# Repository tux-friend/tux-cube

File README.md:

# Physics Sensor Cube ESP32-Tux³

11.04.23 Idea for own ESP32 PCB Design  
15.04.23 First sketches with KiCad  
16.04.23 Idea for physics sensor cube Tux³ and first sketches  
17.04.23 Design and order of v0.1 PCB  
22.04.23 First prototype and proof of concept  
23.04.23 Case v0.1  
25.04.23 Design and order of v0.2 PCB  
25.04.23 Case v0.2  
29.04.23 Software v0.1  
03.05.23 Arrival of PCB v0.1 + v0.2  
10.05.23 Arrival of all parts for PCB, first working ESP32-C3 board  
11.05.23 Order of 30 pcs v0.2 PCB on JLCPCB  
12.05.23 Forth ESP32-C3 board completed  
13.05.23 Case v0.3  
14.05.23 First full prototype &rarr; case too small  
17.05.23 Case v0.4  
21.05.23 ESP32-C3-Tux Mini PCB 20x20mm  
22.05.23 Case v0.5  
27.05.23 Finished DIY Reflow Heat Plate  
31.05.23 Put ESP32-Tux on Tindie and got promotion by [hackster.io](https://www.hackster.io/news/the-lifex-esp32-tux-mini-offers-a-tiny-path-to-energy-harvesting-experimentation-with-an-esp32-c3-0470bf924f33) :-)  
03.06.23 Finished 12 ESP32-Tux Dev boards for Tindie orders  
13.02.24 Designed a ESP32-Tux Board with TP4056 Charging circuit  
15.03.26 Finally got time to get back in the project and designed a new Dev Board with ESP32-C5 chip  

This is an idea I had for some time after playing around with the ESP32 together with sensors, micropython and Phyphox. I started designing a PCB by my own for an ESP32-C3 chip. I want it to be as small as possible and also solar powered. The cube should be energy ,self-sufficient' and used for teaching physics. 

The cube should have the following sensors:
- Temperature, pressure and humidity sensor &rarr; BME280
- Gyroscope for acceleration and orientation measurements &rarr; MPU9250
- Optical/Light sensor (measuring Lux) &rarr; VEML7700
- 2 connectors for temperature probes (DS18B20)
- Voltage and current meter &rarr; INA219
- Time of flight sensor for measuring distances &rarr; VL53L1X
- optional: magnetometer & microphone for sound measurements

In addition the cube should have:
- OLED Display for showing current measurement data/sensor
- RGB-LED (e.g. for showing battery status)
- Push button for changing the sensor/measurement
- Solar cell and LiPo battery
- Pin-header for connecting to cube to a breadboard and use the GPIO Pins
- Mounting nut for placing the cube on a tripod
- On/Off-Button
- optional: buzzer for sound output

I aim for a 35x35x35mm cube with 3D printed case. The case should be robust - so that it can fall from a building and be undamaged... Hope to be able to do this project. 

My inspiration come from the [ESP32-Picoclick-C3](https://github.com/makermoekoe/Picoclick-C3), [BQ25504 Solar Cell LiPo Charger](https://hackaday.io/project/158837-ultra-low-power-lipo-charger-via-energy-harvesting), [01Space-ESP32-C3](https://github.com/01Space/ESP32-C3-0.42LCD) and the [Wemos C3 Pico](https://www.wemos.cc/en/latest/c3/c3_pico.html).

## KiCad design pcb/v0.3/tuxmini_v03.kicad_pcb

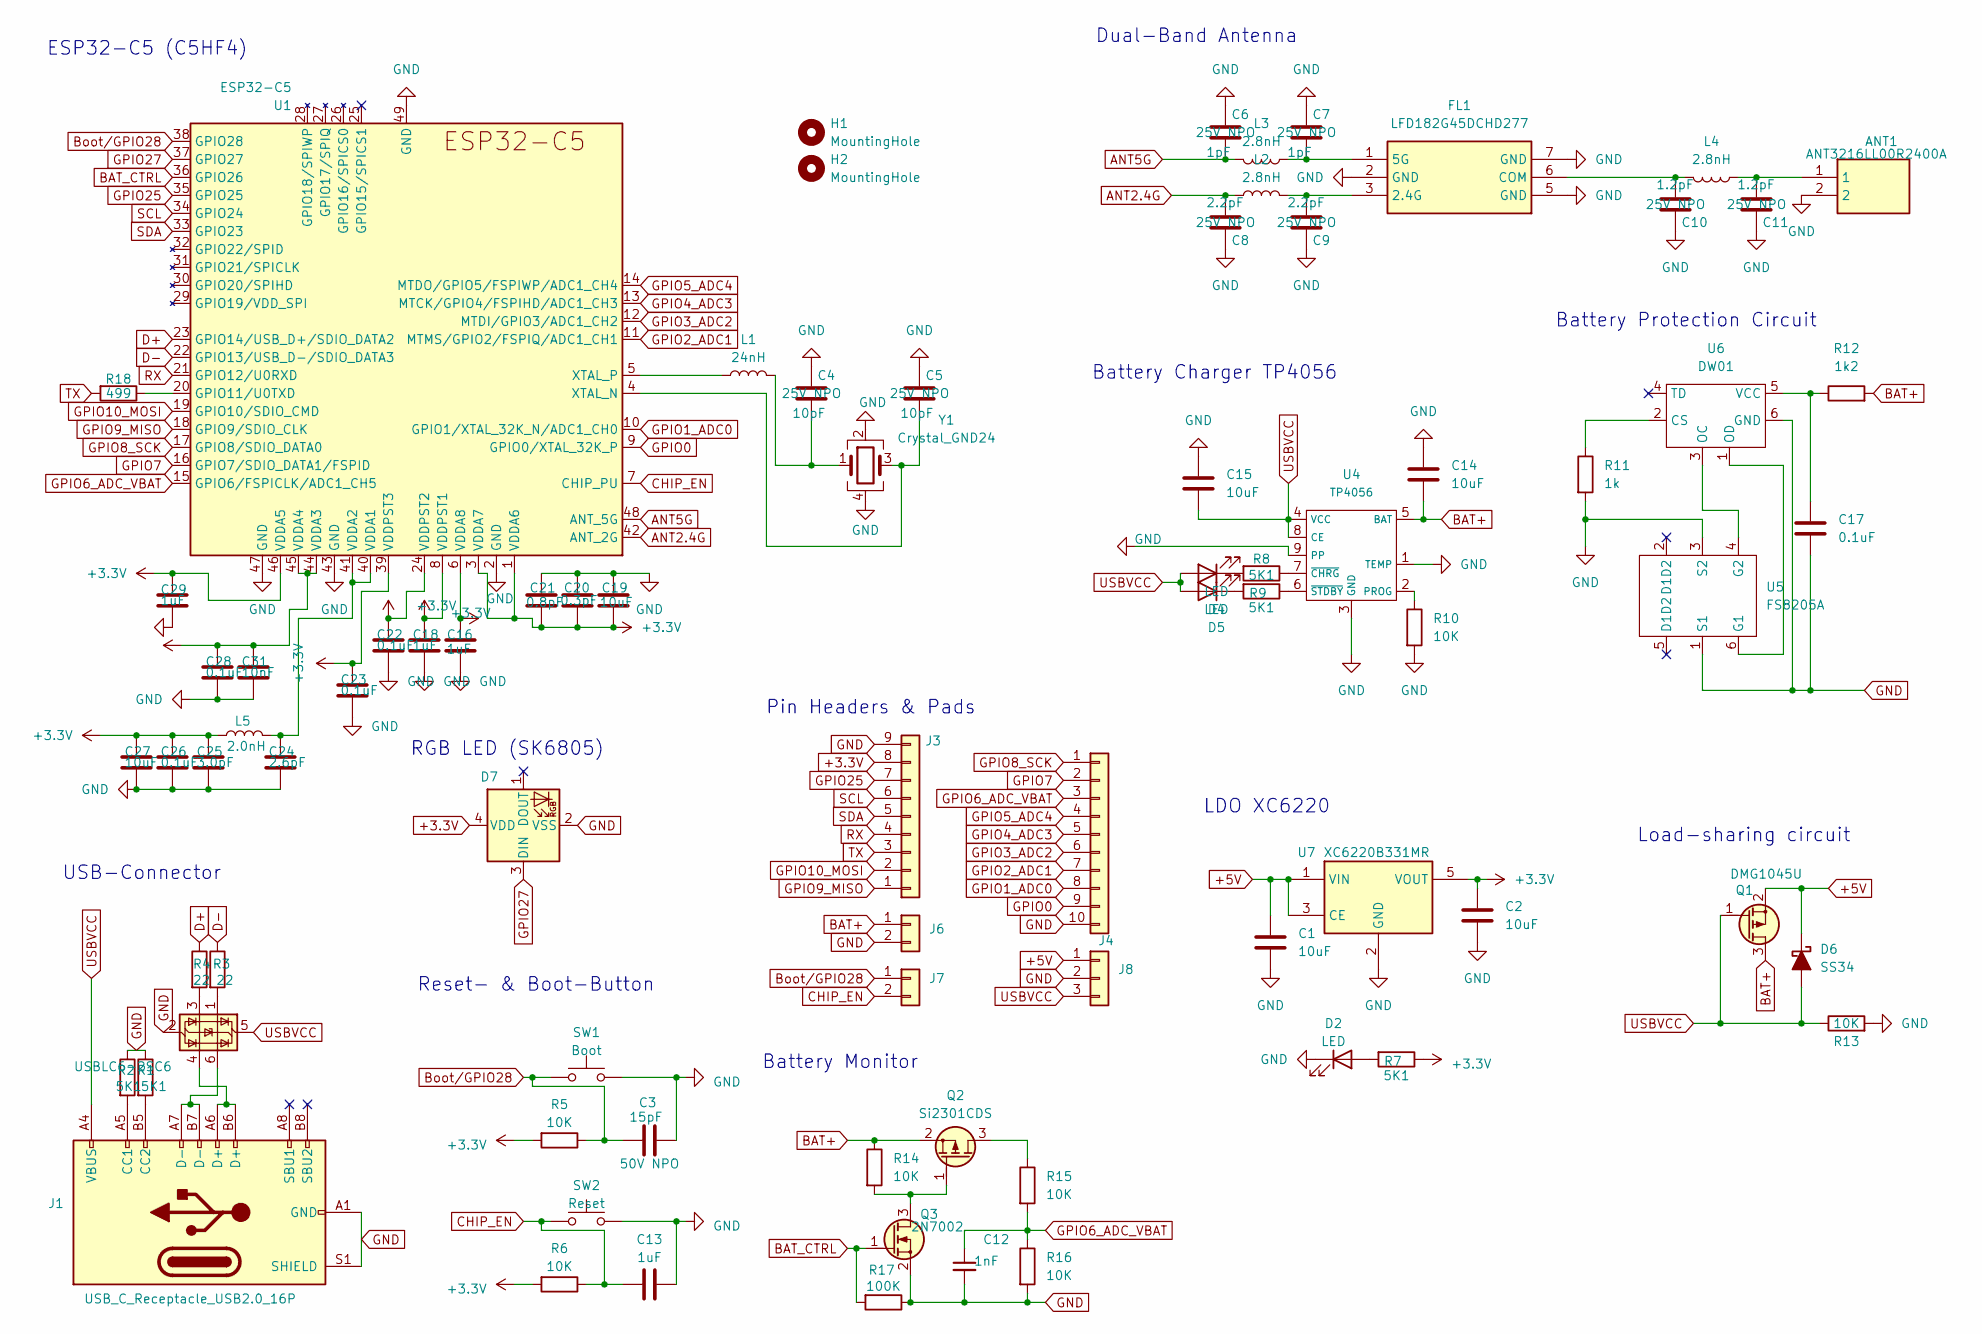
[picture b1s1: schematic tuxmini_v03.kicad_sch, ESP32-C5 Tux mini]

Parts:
ANT1: ANT3216LL00R2400A; Johanson_2450AT18x100; Mouser Part Number 603-ANT3216LL00R2400
C1, C2, C14, C15, C19, C27: 10uF; C_0402_1005Metric
C3: 15pF; C_0402_1005Metric
C4, C5: 10pF; C_0402_1005Metric
C6, C7: 1pF; C_0402_1005Metric
C8, C9: 2.2pF; C_0402_1005Metric
C10, C11: 1.2pF; C_0402_1005Metric
C12: 1nF; C_0402_1005Metric; Tolerance 100%
C13, C16, C18, C29: 1uF; C_0402_1005Metric
C17, C22, C23, C26, C28: 0.1uF; C_0402_1005Metric
C20: 0.3pF; C_0402_1005Metric
C21: 0.8pF; C_0402_1005Metric
C24: 2.6pF; C_0402_1005Metric
C25: 3.0pF; C_0402_1005Metric
C31: 10nF; C_0402_1005Metric
D2, D4, D5: LED; LED_0402_1005Metric
D6: SS34; D_SOD-523
D7: SK6805; LED_SK6812_EC15_1.5x1.5mm
FL1: LFD182G45DCHD277; Manufacturer_Part_Number LFD182G45DCHD277
H1, H2: MountingHole; MountingHole_2.5mm_Pad_Via
J1: USB_C_Receptacle_USB2.0_16P; USB_C_Receptacle_Palconn_UTC16-G
J3: Conn_01x09; PinHeader_1x09_P2.54mm_Vertical
J4: Conn_01x10; PinHeader_1x10_P2.54mm_Vertical
J6: Conn_01x02; PinHeader_1x02_P2.54mm_Vertical; Part Number 1-0201FBV0T
J7: Conn_01x02; PinHeader_1x02_P2.54mm_Vertical
J8: Conn_01x03; PinHeader_1x03_P2.54mm_Vertical
L1: 24nH; L_0402_1005Metric
L2, L3, L4: 2.8nH; L_0402_1005Metric
L5: 2.0nH; L_0402_1005Metric
Q1: DMG1045U; SOT-23
Q2: Si2301CDS; SOT-23
Q3: 2N7002; SOT-23
R1, R2, R7, R8, R9: 5K1; R_0402_1005Metric
R3, R4: 22; R_0402_1005Metric
R5, R6, R10, R13, R14, R15, R16: 10K; R_0402_1005Metric
R11: 1k; R_0402_1005Metric
R12: 1k2; R_0402_1005Metric
R17: 100K; R_0402_1005Metric
R18: 499; R_0402_1005Metric
SW1: Boot; SW_Push_1P1T_NO_CK_KMR2
SW2: Reset; SW_Push_1P1T_NO_CK_KMR2
U1: ESP32-C5; QFN-48-1EP_6x6mm_P0.4mm_EP4.6x4.6mm
U2: USBLC6-2SC6; SOT-23-6
U4: TP4056; SOIC-8-1EP_3.9x4.9mm_P1.27mm_EP2.29x3mm
U5: FS8205A; SOT-23-6
U6: DW01; SOT-23-6
U7: XC6220B331MR; SOT-23-5
Y1: Crystal_GND24; Crystal_SMD_2016-4Pin_2.0x1.6mm

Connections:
+3.3V: C2.1, C16.1, C18.1, C19.2, C20.2, C21.2, C22.1, C23.1, C25.1, C26.1, C27.1, C28.1, C29.1, C31.1, D7.4 (VDD), J3.8, L5.2, R5.2, R6.2, R7.1, U1.1 (VDDA6), U1.3 (VDDA7), U1.6 (VDDA8), U1.8 (VDDPST1), U1.24 (VDDPST2), U1.39 (VDDPST3), U1.44 (VDDA3), U1.45 (VDDA4), U1.46 (VDDA5), U7.5 (VOUT)
+5V: C1.1, D6.1 (K), J8.1, Q1.2 (S), U7.1 (VIN), U7.3 (CE)
ANT2.4G: C8.2, L2.2, U1.42 (ANT_2G)
ANT5G: C6.2, L3.2, U1.48 (ANT_5G)
BAT+: C14.2, J6.1, Q1.3 (D), Q2.2 (S), R12.2, R14.1, U4.5 (BAT)
BAT_CTRL: Q3.1 (G), R17.2, U1.36 (GPIO26)
Boot/GPIO28: C3.1, J7.1, R5.1, SW1.1, U1.38 (GPIO28)
CHIP_EN: C13.1, J7.2, R6.1, SW2.1, U1.7 (CHIP_PU)
D+: R4.1, U1.23 (GPIO14/USB_D+/SDIO_DATA2)
D-: R3.1, U1.22 (GPIO13/USB_D-/SDIO_DATA3)
GND: ANT1.2, C1.2, C2.2, C3.2, C4.1, C5.1, C6.1, C7.1, C8.1, C9.1, C10.1, C11.1, C12.2, C13.2, C14.1, C15.1, C16.2, C17.2, C18.2, C19.1, C20.1, C21.1, C22.2, C23.2, C24.2, C25.2, C26.2, C27.2, C28.2, C29.2, C31.2, D2.1 (K), D7.2 (VSS), FL1.2 (GND), FL1.5 (GND), FL1.7 (GND), J1.A1 (GND), J1.A12 (GND), J1.B1 (GND), J1.B12 (GND), J1.S1 (SHIELD), J3.9, J4.10, J6.2, J8.2, Q3.2 (S), R1.1, R2.1, R10.2, R11.2, R13.2, R16.2, R17.1, SW1.2, SW2.2, U1.2 (GND), U1.43 (GND), U1.47 (GND), U1.49 (GND), U2.2 (GND), U4.1 (TEMP), U4.3 (GND), U4.9 (PP), U5.1 (S1), U5.3 (S2), U6.6 (GND), U7.2 (GND), Y1.2, Y1.4
GPIO0: J4.9, U1.9 (GPIO0/XTAL_32K_P)
GPIO1_ADC0: J4.8, U1.10 (GPIO1/XTAL_32K_N/ADC1_CH0)
GPIO2_ADC1: J4.7, U1.11 (MTMS/GPIO2/FSPIQ/ADC1_CH1)
GPIO3_ADC2: J4.6, U1.12 (MTDI/GPIO3/ADC1_CH2)
GPIO4_ADC3: J4.5, U1.13 (MTCK/GPIO4/FSPIHD/ADC1_CH3)
GPIO5_ADC4: J4.4, U1.14 (MTDO/GPIO5/FSPIWP/ADC1_CH4)
GPIO6_ADC_VBAT: C12.1, J4.3, R15.2, R16.1, U1.15 (GPIO6/FSPICLK/ADC1_CH5)
GPIO7: J4.2, U1.16 (GPIO7/SDIO_DATA1/FSPID)
GPIO8_SCK: J4.1, U1.17 (GPIO8/SDIO_DATA0)
GPIO9_MISO: J3.1, U1.18 (GPIO9/SDIO_CLK)
GPIO10_MOSI: J3.2, U1.19 (GPIO10/SDIO_CMD)
GPIO25: J3.7, U1.35 (GPIO25)
GPIO27: D7.3 (DIN), U1.37 (GPIO27)
unnamed: ANT1.1, C11.2, L4.2
unnamed: C4.2, L1.2, Y1.1
unnamed: D2.2 (A), R7.2
unnamed: D4.1 (K), R8.2
unnamed: D5.1 (K), R9.2
unnamed: C9.2, FL1.3 (2.4G), L2.1
unnamed: C7.2, FL1.1 (5G), L3.1
unnamed: C10.2, FL1.6 (COM), L4.1
unnamed: J1.A5 (CC1), R2.2
unnamed: J1.B5 (CC2), R1.2
unnamed: J1.A6 (D+), J1.B6 (D+), U2.4 (I/O2)
unnamed: J1.A7 (D-), J1.B7 (D-), U2.6 (I/O1)
unnamed: Q2.3 (D), R15.1
unnamed: Q2.1 (G), Q3.3 (D), R14.2
unnamed: R3.2, U2.1 (I/O1)
unnamed: R4.2, U2.3 (I/O2)
unnamed: R18.1, U1.20 (GPIO11/U0TXD)
unnamed: C24.1, L5.1, U1.40 (VDDA1), U1.41 (VDDA2)
unnamed: C5.2, U1.4 (XTAL_N), Y1.3
unnamed: L1.1, U1.5 (XTAL_P)
unnamed: R10.1, U4.2 (PROG)
unnamed: R8.1, U4.7 (~CHRG)
unnamed: R9.1, U4.6 (~STDBY)
unnamed: U5.6 (G1), U6.1 (OD)
unnamed: U5.4 (G2), U6.3 (OC)
unnamed: R11.1, U6.2 (CS)
unnamed: C17.1, R12.1, U6.5 (VCC)
RX: J3.4, U1.21 (GPIO12/U0RXD)
SCL: J3.6, U1.34 (GPIO24)
SDA: J3.5, U1.33 (GPIO23)
TX: J3.3, R18.2
USBVCC: C15.2, D4.2 (A), D5.2 (A), D6.2 (A), J1.A4 (VBUS), J1.A9 (VBUS), J1.B4 (VBUS), J1.B9 (VBUS), J8.3, Q1.1 (G), R13.1, U2.5 (VBUS), U4.4 (VCC), U4.8 (CE)

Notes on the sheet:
Reset- & Boot-Button
Battery Monitor
Battery Protection Circuit
LDO XC6220
Load-sharing circuit
Pin Headers & Pads
RGB LED (SK6805)
USB-Connector
ESP32-C5 (C5HF4)
Battery Charger TP4056
Dual-Band Antenna

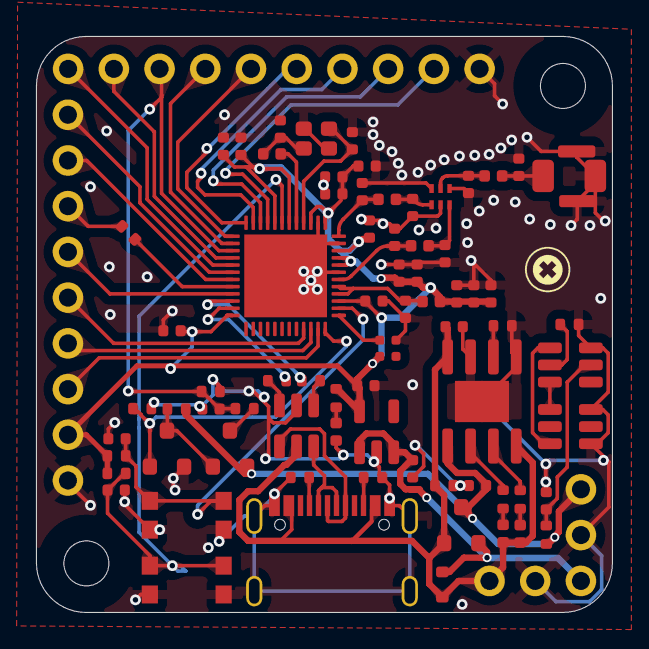
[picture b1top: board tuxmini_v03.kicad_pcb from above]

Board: 2 copper layers, 32.0 x 32.0 mm, 80 parts (1 on the bottom side), 56 nets.

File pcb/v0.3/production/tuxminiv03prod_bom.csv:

Designator,Footprint,Quantity,Value,LCSC Part #
ANT1,Johanson_2450AT18x100,1,ANT3216LL00R2400A,
"C1, C14, C15, C19, C2, C27",0402,6,10uF,
"C10, C11",0402,2,1.2pF,
C12,0402,1,1nF,
"C13, C16, C18, C29",0402,4,1uF,
"C17, C22, C23, C26, C28",0402,5,0.1uF,
C20,0402,1,0.3pF,
C21,0402,1,0.8pF,
C24,0402,1,2.6pF,
C25,0402,1,3.0pF,
C3,0402,1,15pF,
C31,0402,1,10nF,
"C4, C5",0402,2,10pF,
"C6, C7",0402,2,1pF,
"C8, C9",0402,2,2.2pF,
"D2, D4, D5",0402,3,LED,
D6,D_SOD-523,1,SS34,
D7,LED_SK6812_EC15_1.5x1.5mm,1,SK6805,
FL1,LFD182G45DCHD277,1,LFD182G45DCHD277,
J1,USB_C_Receptacle_Palconn_UTC16-G,1,USB_C_Receptacle_USB2.0_16P,
J3,PinHeader_1x09_P2.54mm_Vertical,1,Conn_01x09,
J4,PinHeader_1x10_P2.54mm_Vertical,1,Conn_01x10,
"J6, J7",PinHeader_1x02_P2.54mm_Vertical,2,Conn_01x02,
J8,PinHeader_1x03_P2.54mm_Vertical,1,Conn_01x03,
L1,0402,1,24nH,
"L2, L3, L4",0402,3,2.8nH,
L5,0402,1,2.0nH,
Q1,SOT-23,1,DMG1045U,
Q2,SOT-23,1,Si2301CDS,
Q3,SOT-23,1,2N7002,
"R1, R2, R7, R8, R9",0402,5,5K1,
"R10, R13, R14, R15, R16, R5, R6",0402,7,10K,
R11,0402,1,1k,
R12,0402,1,1k2,
R17,0402,1,100K,
R18,0402,1,499,
"R3, R4",0402,2,22,
SW1,SW_Push_1P1T_NO_CK_KMR2,1,Boot,
SW2,SW_Push_1P1T_NO_CK_KMR2,1,Reset,
U1,QFN-48-1EP_6x6mm_P0.4mm_EP4.6x4.6mm,1,ESP32-C5,
U2,SOT-23-6,1,USBLC6-2SC6,
U4,SOIC-8-1EP_3.9x4.9mm_P1.27mm_EP2.29x3mm,1,TP4056,
U5,SOT-23-6,1,FS8205A,
U6,SOT-23-6,1,DW01,
U7,SOT-23-5,1,XC6220B331MR,
Y1,Crystal_SMD_2016-4Pin_2.0x1.6mm,1,Crystal_GND24,

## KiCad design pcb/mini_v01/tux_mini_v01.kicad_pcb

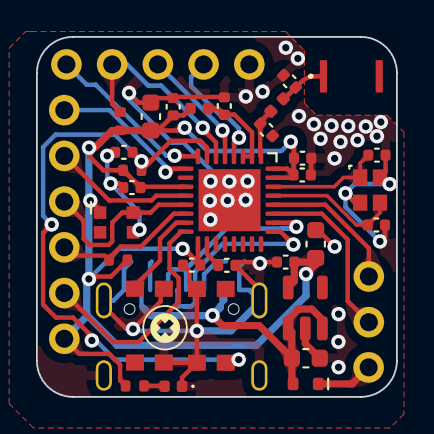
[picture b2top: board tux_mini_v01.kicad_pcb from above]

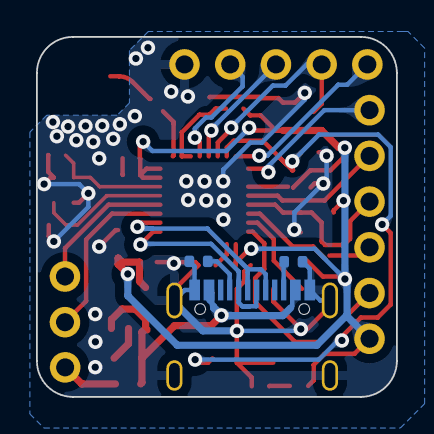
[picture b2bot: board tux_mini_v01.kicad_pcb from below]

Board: 2 copper layers, 20.0 x 20.0 mm, 38 parts (3 on the bottom side), 27 nets.

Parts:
ANT1: ANT3216LL00R2400A
C1, C3: 10 pF; C_0402_1005Metric
C2, C10, C13, C20: 1 uF; C_0402_1005Metric
C4, C5, C9, C11: 0.1 uF; C_0402_1005Metric
C6: 4.7 pF; C_0402_1005Metric
C7: 3.3 pF; C_0402_1005Metric
C8: 10 nF; C_0402_1005Metric
C12, C16, C19: 10 uF; C_0603_1608Metric
D1: LED; LED_0402_1005Metric
D2: 1N4148WT; D_SOD-523
D3: WS2812B; LED_WS2812B-2020_PLCC4_2.0x2.0mm
J1: USB_C_Receptacle_USB2.0; USB_C_Receptacle_Palconn_UTC16-G
J2: Conn_02x04_Top_Bottom; PinHeader_1x06_P2.54mm_Vertical
J3: Conn_02x04_Top_Bottom; PinHeader_1x05_P2.54mm_Vertical
J4: Conn_01x02; PinHeader_1x02_P2.54mm_Vertical
J5: Conn_01x01; PinHeader_1x01_P2.54mm_Vertical
L1, L2: 2 nH; L_0402_1005Metric
R1, R5, R6: 10K; R_0402_1005Metric
R2, R3: 5k1; R_0402_1005Metric
R4: 1K; R_0402_1005Metric
SW1: Boot; SW_Push_1P1T_NO_CK_KMR2
SW2: Reset; SW_Push_1P1T_NO_CK_KMR2
U1: ESP32-C3; QFN-32-1EP_5x5mm_P0.5mm_EP3.45x3.45mm
U3: SPX3819M5-L-3-3; SOT-23-5
Y1: 40 Mhz; Crystal_SMD_2016-4Pin_2.0x1.6mm

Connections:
+3.3V: C4.1, C5.1, C8.1, C10.1, C11.2, C12.2, C19.1, C20.1, D3.1 (VDD), J2.6, L2.2, R1.2, R4.2, R5.2, R6.2, U1.11 (VDD3P3_RTC), U1.17 (VDD3P3_CPU), U1.31 (VDDA), U1.32 (VDDA), U3.5 (OUT)
+5V: C16.1, D2.1 (K), D2.2 (A), J1.A4 (VBUS), J1.A9 (VBUS), J1.B4 (VBUS), J1.B9 (VBUS), J5.1, U3.1 (IN), U3.3 (EN)
ANT1: ANT1.1, C7.1, L1.2
CHIP_EN: C13.1, R6.1, SW2.1, U1.7 (CHIP_EN)
GND: C1.2, C2.2, C3.1, C4.2, C5.2, C6.2, C7.2, C8.2, C9.1, C10.2, C11.1, C12.1, C13.2, C16.2, C19.2, C20.2, D1.1 (K), D3.3 (VSS), J1.A1 (GND), J1.A12 (GND), J1.B1 (GND), J1.B12 (GND), J1.S1 (SHIELD), J3.5, R2.1, R3.1, SW1.2, SW2.2, U1.33 (GND), U3.2 (GND), Y1.2, Y1.4
IO0: J3.4, U1.4 (XTAL_32K_P/ADC1_CH0)
IO1: J3.3, U1.5 (XTAL_32K_N/ADC1_CH1)
IO2: J3.2, R5.1, U1.6 (GPIO2/ADC1_CH2)
IO3: J3.1, U1.8 (GPIO3/ADC1_CH3)
IO4: J2.1, U1.9 (MTMS/GPIO4/ADC1_CH4)
IO6: J2.2, U1.12 (MTCK/GPIO6)
IO7: D3.4 (DIN), J2.3, U1.13 (MTDO/GPIO7)
IO8: J2.4, R1.1, U1.14 (GPIO8)
IO9: SW1.1, U1.15 (GPIO9/BOOT)
IO10: J2.5, U1.16 (GPIO10)
IO18: J1.A7 (D-), J1.B7 (D-), U1.25 (GPIO18/USB_D-)
IO19: J1.A6 (D+), J1.B6 (D+), U1.26 (GPIO19/USB_D+)
unnamed: C9.2, L2.1, U1.2 (VDD3P3), U1.3 (VDD3P3)
unnamed: D1.2 (A), R4.1
unnamed: J1.A5 (CC1), R2.2
unnamed: J1.B5 (CC2), R3.2
unnamed: C6.1, L1.1, U1.1 (LNA_IN)
RX: J4.2, U1.27 (U0RXD/GPIO20)
TX: J4.1, U1.28 (U0TXD/GPIO21)
VDD_SPI: C2.1, U1.18 (VDD_SPI/GPIO11)
XTAL_N: C3.2, U1.29 (XTAL_N), Y1.3
XTAL_P: C1.1, U1.30 (XTAL_P), Y1.1

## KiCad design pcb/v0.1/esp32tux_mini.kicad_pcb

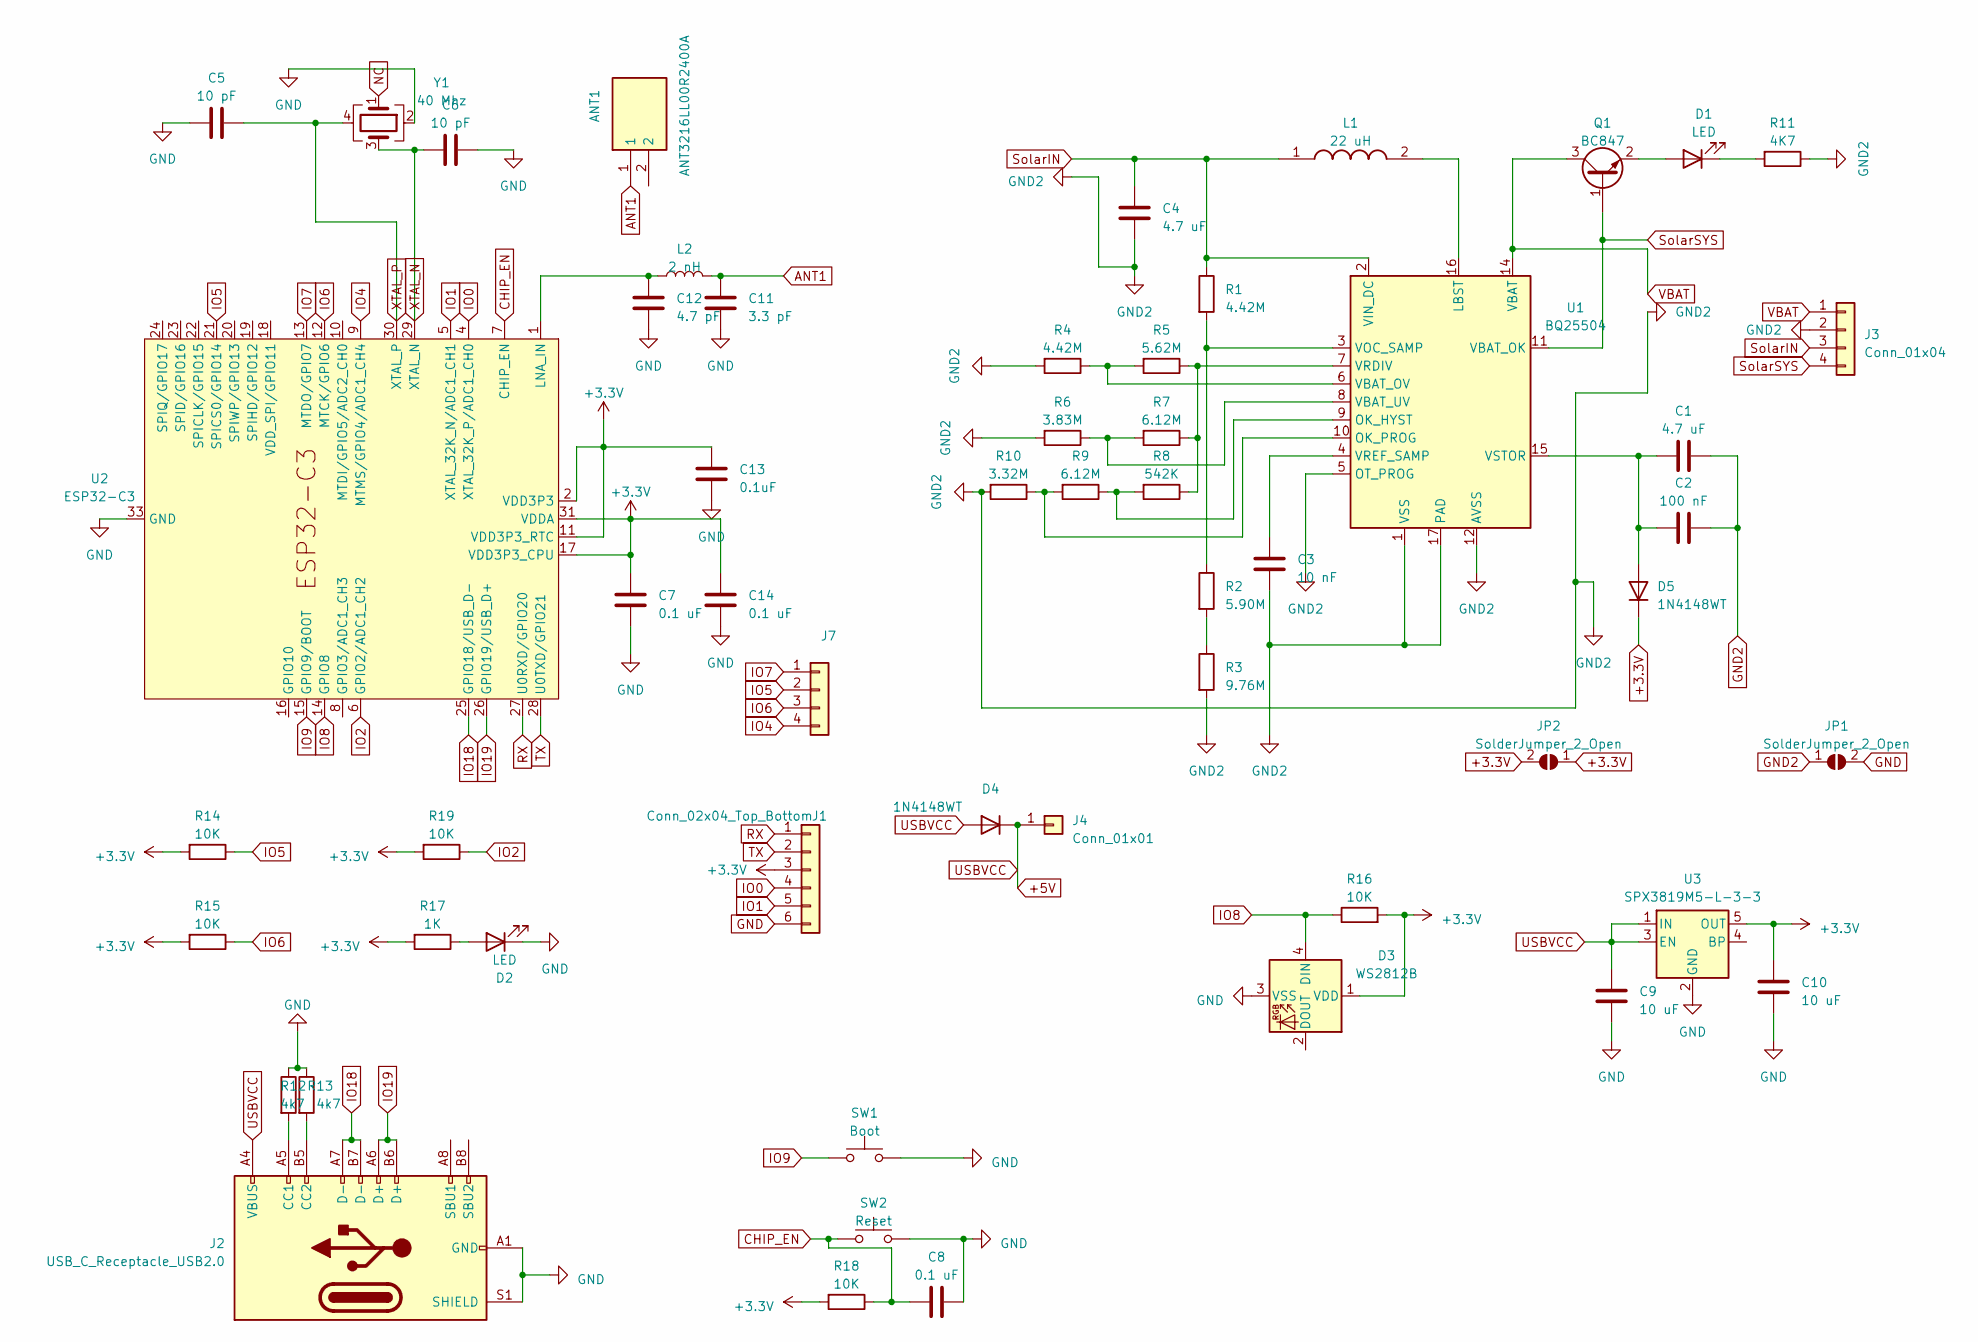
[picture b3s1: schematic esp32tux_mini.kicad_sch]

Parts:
ANT1: ANT3216LL00R2400A; Mouser Part Number 603-ANT3216LL00R2400
C1, C4: 4.7 uF; C_0603_1608Metric
C2: 100 nF; C_0402_1005Metric
C3: 10 nF; C_0402_1005Metric
C5, C6: 10 pF; C_0402_1005Metric
C7, C8, C14: 0.1 uF; C_0402_1005Metric
C9, C10: 10 uF; C_0603_1608Metric
C11: 3.3 pF; C_0402_1005Metric
C12: 4.7 pF; C_0402_1005Metric
C13: 0.1uF; C_0402_1005Metric
D1, D2: LED; LED_0402_1005Metric
D3: WS2812B; LED_WS2812B-2020_PLCC4_2.0x2.0mm
D4, D5: 1N4148WT; D_SOD-523
J1: Conn_02x04_Top_Bottom; PinHeader_1x06_P2.54mm_Vertical
J2: USB_C_Receptacle_USB2.0; USB_C_Receptacle_Palconn_UTC16-G
J3: Conn_01x04; PinHeader_1x04_P2.54mm_Vertical
J4: Conn_01x01; PinHeader_1x01_P2.54mm_Vertical
J7: Conn_02x04_Top_Bottom; PinHeader_1x04_P2.54mm_Vertical
JP1, JP2: SolderJumper_2_Open; SolderJumper-2_P1.3mm_Open_Pad1.0x1.5mm
L1: 22 uH; L_1008_2520Metric; Mouser Part Number 963-BRC2518T220K
L2: 2 nH; L_0402_1005Metric
Q1: BC847; SOT-23
R1, R4: 4.42M; R_0402_1005Metric
R2: 5.90M; R_0402_1005Metric
R3: 9.76M; R_0402_1005Metric
R5: 5.62M; R_0402_1005Metric
R6: 3.83M; R_0402_1005Metric
R7, R9: 6.12M; R_0402_1005Metric
R8: 542K; R_0402_1005Metric
R10: 3.32M; R_0402_1005Metric
R11: 4K7; R_0402_1005Metric
R12, R13: 4k7; R_0402_1005Metric
R14, R15, R16, R18, R19: 10K; R_0402_1005Metric
R17: 1K; R_0402_1005Metric
SW1: Boot; SW_Push_1P1T_NO_CK_KMR2
SW2: Reset; SW_Push_1P1T_NO_CK_KMR2
U1: BQ25504; VQFN-16-1EP_3x3mm_P0.5mm_EP1.68x1.68mm
U2: ESP32-C3; QFN-32-1EP_5x5mm_P0.5mm_EP3.45x3.45mm
U3: SPX3819M5-L-3-3; SOT-23-5
Y1: 40 Mhz; Crystal_SMD_3225-4Pin_3.2x2.5mm

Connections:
+3.3V: C7.1, C10.1, C13.1, C14.1, D3.1 (VDD), D5.1 (K), J1.3, JP2.1 (A), JP2.2 (B), R14.2, R15.2, R16.2, R17.2, R18.2, R19.2, U2.2 (VDD3P3), U2.3 (VDD3P3), U2.11 (VDD3P3_RTC), U2.17 (VDD3P3_CPU), U2.31 (VDDA), U2.32 (VDDA), U3.5 (OUT)
+5V: C9.1, D4.1 (K), D4.2 (A), J2.A4 (VBUS), J2.A9 (VBUS), J2.B4 (VBUS), J2.B9 (VBUS), J4.1, U3.1 (IN), U3.3 (EN)
ANT1: ANT1.1, C11.1, L2.2
CHIP_EN: C8.1, R18.1, SW2.1, U2.7 (CHIP_EN)
GND: C5.2, C6.1, C7.2, C8.2, C9.2, C10.2, C11.2, C12.2, C13.2, C14.2, D2.1 (K), D3.3 (VSS), J1.6, J2.A1 (GND), J2.A12 (GND), J2.B1 (GND), J2.B12 (GND), J2.S1 (SHIELD), JP1.2 (B), R12.1, R13.1, SW1.2, SW2.2, U2.33 (GND), U3.2 (GND), Y1.2
GND2: C1.2, C2.2, C3.2, C4.2, J3.2, JP1.1 (A), R3.2, R4.2, R6.2, R10.2, R11.1, U1.1 (VSS), U1.5 (OT_PROG), U1.12 (AVSS), U1.13 (VSS), U1.17 (PAD)
IO0: J1.4, U2.4 (XTAL_32K_P/ADC1_CH0)
IO1: J1.5, U2.5 (XTAL_32K_N/ADC1_CH1)
IO2: R19.1, U2.6 (GPIO2/ADC1_CH2)
IO4: J7.4, U2.9 (MTMS/GPIO4/ADC1_CH4)
IO5: J7.2, R14.1, U2.21 (SPICS0/GPIO14)
IO6: J7.3, R15.1, U2.12 (MTCK/GPIO6)
IO7: J7.1, U2.13 (MTDO/GPIO7)
IO8: D3.4 (DIN), R16.1, U2.14 (GPIO8)
IO9: SW1.1, U2.15 (GPIO9/BOOT)
IO18: J2.A7 (D-), J2.B7 (D-), U2.25 (GPIO18/USB_D-)
IO19: J2.A6 (D+), J2.B6 (D+), U2.26 (GPIO19/USB_D+)
NC: Y1.1
unnamed: D1.2 (A), Q1.2 (E)
unnamed: D1.1 (K), R11.2
unnamed: D2.2 (A), R17.1
unnamed: C1.1, C2.1, D5.2 (A), U1.15 (VSTOR)
unnamed: J2.A5 (CC1), R12.2
unnamed: J2.B5 (CC2), R13.2
unnamed: R2.2, R3.1
unnamed: L1.2, U1.16 (LBST)
unnamed: R8.2, R9.1, U1.9 (OK_HYST)
unnamed: R9.2, R10.1, U1.10 (OK_PROG)
unnamed: R4.1, R5.2, U1.6 (VBAT_OV)
unnamed: R6.1, R7.2, U1.8 (VBAT_UV)
unnamed: R1.2, R2.1, U1.3 (VOC_SAMP)
unnamed: R5.1, R7.1, R8.1, U1.7 (VRDIV)
unnamed: C3.1, U1.4 (VREF_SAMP)
unnamed: C12.1, L2.1, U2.1 (LNA_IN)
RX: J1.1, U2.27 (U0RXD/GPIO20)
SolarIN: C4.1, J3.3, L1.1, R1.1, U1.2 (VIN_DC)
SolarSYS: J3.4, Q1.1 (B), U1.11 (VBAT_OK)
TX: J1.2, U2.28 (U0TXD/GPIO21)
VBAT: J3.1, Q1.3 (C), U1.14 (VBAT)
XTAL_N: C6.2, U2.29 (XTAL_N), Y1.3
XTAL_P: C5.1, U2.30 (XTAL_P), Y1.4

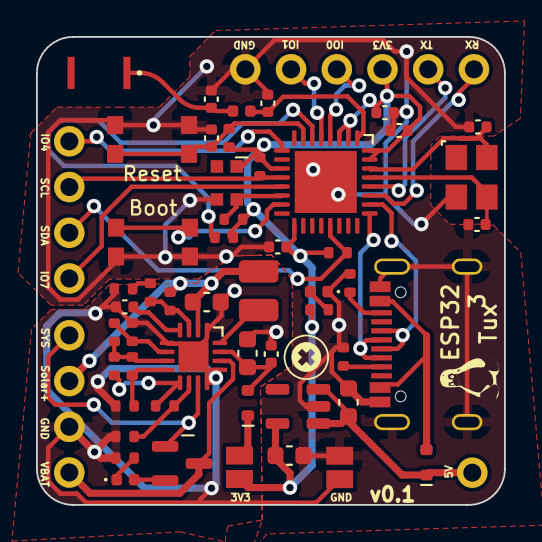
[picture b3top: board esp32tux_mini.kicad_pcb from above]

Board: 2 copper layers, 26.0 x 26.0 mm, 55 parts (0 on the bottom side), 40 nets.

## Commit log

2023-04-19 Add files via upload
    ESP32 first PCB Design v0.1
2023-04-19 Add files via upload
    PDF of schematics
2023-04-24 FreeCAD design and stl files of first case draft
2023-04-24 proof of concept images
2023-04-25 case v02
2023-04-29 First Software version for tux cube
2023-05-22 ESP32-Tux-Mini v01 PCB
    Mini PCB without BQ25504 solar charging circuit, 20x20mm
2026-03-15 PCB v0.3 with ESP32-C5 chip and TP4056
    TP4056 charging circuit instead of BQ25504
2026-03-16 Create LICENCE
2026-03-30 Swaped D- and D+ pin on ESP32-C5 pinout
2026-04-10 Add greeting to README
2026-04-10 Update README header format
2026-04-10 Create esp32-c5
2026-04-12 add schematics as pdf file

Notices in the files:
pcb/v0.3/tuxmini_v03.kicad_pcb:
Licensed under
CERN-OHL-S v2
pcb/v0.3/tuxmini_v03.kicad_sch:
CC BY-SA 4.0
